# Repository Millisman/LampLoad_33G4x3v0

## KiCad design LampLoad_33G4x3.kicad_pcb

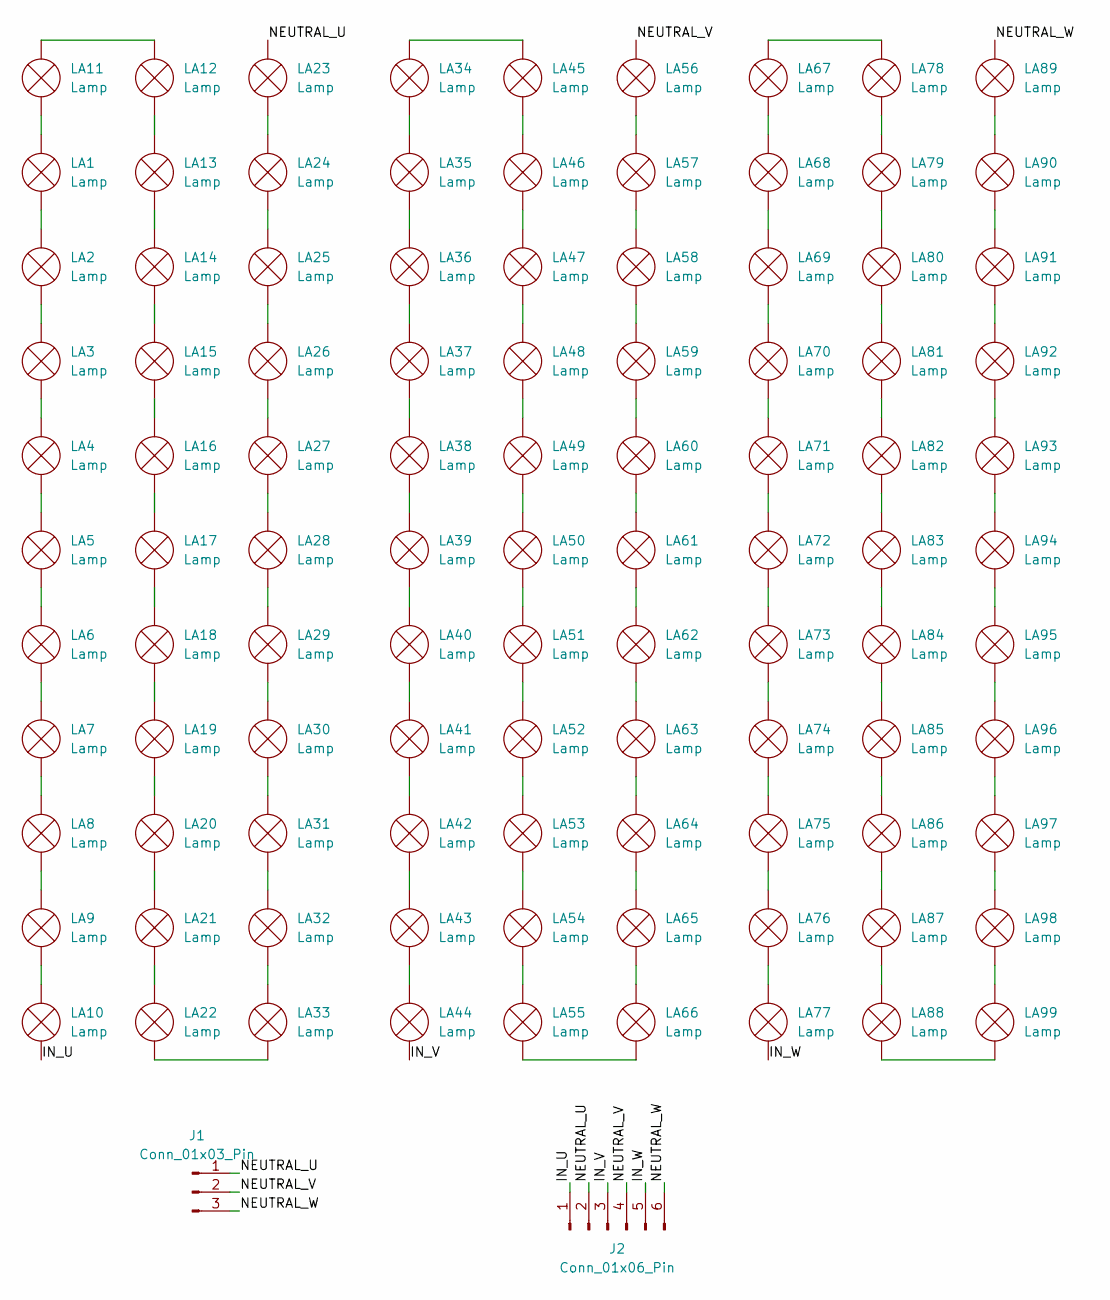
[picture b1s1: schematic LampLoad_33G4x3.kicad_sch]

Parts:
J1: Conn_01x03_Pin; PhoenixContact_MC_1,5_3-G-5.08_1x03_P5.08mm_Horizontal
J2: Conn_01x06_Pin; PhoenixContact_MC_1,5_6-G-5.08_1x06_P5.08mm_Horizontal
LA1, LA2, LA3, LA4, LA5, LA6, LA7, LA8, LA9, LA10, LA11, LA12, LA13, LA14, LA15, LA16, LA17, LA18, LA19, LA20, LA21, LA22, LA23, LA24, LA25, LA26, LA27, LA28, LA29, LA30, LA31, LA32, LA33, LA34, LA35, LA36, LA37, LA38, LA39, LA40, LA41, LA42, LA43, LA44, LA45, LA46, LA47, LA48, LA49, LA50, LA51, LA52, LA53, LA54, LA55, LA56, LA57, LA58, LA59, LA60, LA61, LA62, LA63, LA64, LA65, LA66, LA67, LA68, LA69, LA70, LA71, LA72, LA73, LA74, LA75, LA76, LA77, LA78, LA79, LA80, LA81, LA82, LA83, LA84, LA85, LA86, LA87, LA88, LA89, LA90, LA91, LA92, LA93, LA94, LA95, LA96, LA97, LA98, LA99: Lamp; PinHeader_1x02_P2.54mm_Vertical

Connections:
/IN_U: J2.1, LA10.1 (-)
/IN_V: J2.3, LA44.1 (-)
/IN_W: J2.5, LA77.1 (-)
/NEUTRAL_U: J1.1, J2.2, LA23.2 (+)
/NEUTRAL_V: J1.2, J2.4, LA56.2 (+)
/NEUTRAL_W: J1.3, J2.6, LA89.2 (+)
unnamed: LA1.2 (+), LA11.1 (-)
unnamed: LA1.1 (-), LA2.2 (+)
unnamed: LA2.1 (-), LA3.2 (+)
unnamed: LA3.1 (-), LA4.2 (+)
unnamed: LA4.1 (-), LA5.2 (+)
unnamed: LA5.1 (-), LA6.2 (+)
unnamed: LA6.1 (-), LA7.2 (+)
unnamed: LA7.1 (-), LA8.2 (+)
unnamed: LA8.1 (-), LA9.2 (+)
unnamed: LA9.1 (-), LA10.2 (+)
unnamed: LA11.2 (+), LA12.2 (+)
unnamed: LA12.1 (-), LA13.2 (+)
unnamed: LA13.1 (-), LA14.2 (+)
unnamed: LA14.1 (-), LA15.2 (+)
unnamed: LA15.1 (-), LA16.2 (+)
unnamed: LA16.1 (-), LA17.2 (+)
unnamed: LA17.1 (-), LA18.2 (+)
unnamed: LA18.1 (-), LA19.2 (+)
unnamed: LA19.1 (-), LA20.2 (+)
unnamed: LA20.1 (-), LA21.2 (+)
unnamed: LA21.1 (-), LA22.2 (+)
unnamed: LA22.1 (-), LA33.1 (-)
unnamed: LA23.1 (-), LA24.2 (+)
unnamed: LA24.1 (-), LA25.2 (+)
unnamed: LA25.1 (-), LA26.2 (+)
unnamed: LA26.1 (-), LA27.2 (+)
unnamed: LA27.1 (-), LA28.2 (+)
unnamed: LA28.1 (-), LA29.2 (+)
unnamed: LA29.1 (-), LA30.2 (+)
unnamed: LA30.1 (-), LA31.2 (+)
unnamed: LA31.1 (-), LA32.2 (+)
unnamed: LA32.1 (-), LA33.2 (+)
unnamed: LA34.2 (+), LA45.2 (+)
unnamed: LA34.1 (-), LA35.2 (+)
unnamed: LA35.1 (-), LA36.2 (+)
unnamed: LA36.1 (-), LA37.2 (+)
unnamed: LA37.1 (-), LA38.2 (+)
unnamed: LA38.1 (-), LA39.2 (+)
unnamed: LA39.1 (-), LA40.2 (+)
unnamed: LA40.1 (-), LA41.2 (+)
unnamed: LA41.1 (-), LA42.2 (+)
unnamed: LA42.1 (-), LA43.2 (+)
unnamed: LA43.1 (-), LA44.2 (+)
unnamed: LA45.1 (-), LA46.2 (+)
unnamed: LA46.1 (-), LA47.2 (+)
unnamed: LA47.1 (-), LA48.2 (+)
unnamed: LA48.1 (-), LA49.2 (+)
unnamed: LA49.1 (-), LA50.2 (+)
unnamed: LA50.1 (-), LA51.2 (+)
unnamed: LA51.1 (-), LA52.2 (+)
unnamed: LA52.1 (-), LA53.2 (+)
unnamed: LA53.1 (-), LA54.2 (+)
unnamed: LA54.1 (-), LA55.2 (+)
unnamed: LA55.1 (-), LA66.1 (-)
unnamed: LA56.1 (-), LA57.2 (+)
unnamed: LA57.1 (-), LA58.2 (+)
unnamed: LA58.1 (-), LA59.2 (+)
unnamed: LA59.1 (-), LA60.2 (+)
unnamed: LA60.1 (-), LA61.2 (+)
unnamed: LA61.1 (-), LA62.2 (+)
unnamed: LA62.1 (-), LA63.2 (+)
unnamed: LA63.1 (-), LA64.2 (+)
unnamed: LA64.1 (-), LA65.2 (+)
unnamed: LA65.1 (-), LA66.2 (+)
unnamed: LA67.2 (+), LA78.2 (+)
unnamed: LA67.1 (-), LA68.2 (+)
unnamed: LA68.1 (-), LA69.2 (+)
unnamed: LA69.1 (-), LA70.2 (+)
unnamed: LA70.1 (-), LA71.2 (+)
unnamed: LA71.1 (-), LA72.2 (+)
unnamed: LA72.1 (-), LA73.2 (+)
unnamed: LA73.1 (-), LA74.2 (+)
unnamed: LA74.1 (-), LA75.2 (+)
unnamed: LA75.1 (-), LA76.2 (+)
unnamed: LA76.1 (-), LA77.2 (+)
unnamed: LA78.1 (-), LA79.2 (+)
unnamed: LA79.1 (-), LA80.2 (+)
unnamed: LA80.1 (-), LA81.2 (+)
unnamed: LA81.1 (-), LA82.2 (+)
unnamed: LA82.1 (-), LA83.2 (+)
unnamed: LA83.1 (-), LA84.2 (+)
unnamed: LA84.1 (-), LA85.2 (+)
unnamed: LA85.1 (-), LA86.2 (+)
unnamed: LA86.1 (-), LA87.2 (+)
unnamed: LA87.1 (-), LA88.2 (+)
unnamed: LA88.1 (-), LA99.1 (-)
unnamed: LA89.1 (-), LA90.2 (+)
unnamed: LA90.1 (-), LA91.2 (+)
unnamed: LA91.1 (-), LA92.2 (+)
unnamed: LA92.1 (-), LA93.2 (+)
unnamed: LA93.1 (-), LA94.2 (+)
unnamed: LA94.1 (-), LA95.2 (+)
unnamed: LA95.1 (-), LA96.2 (+)
unnamed: LA96.1 (-), LA97.2 (+)
unnamed: LA97.1 (-), LA98.2 (+)
unnamed: LA98.1 (-), LA99.2 (+)

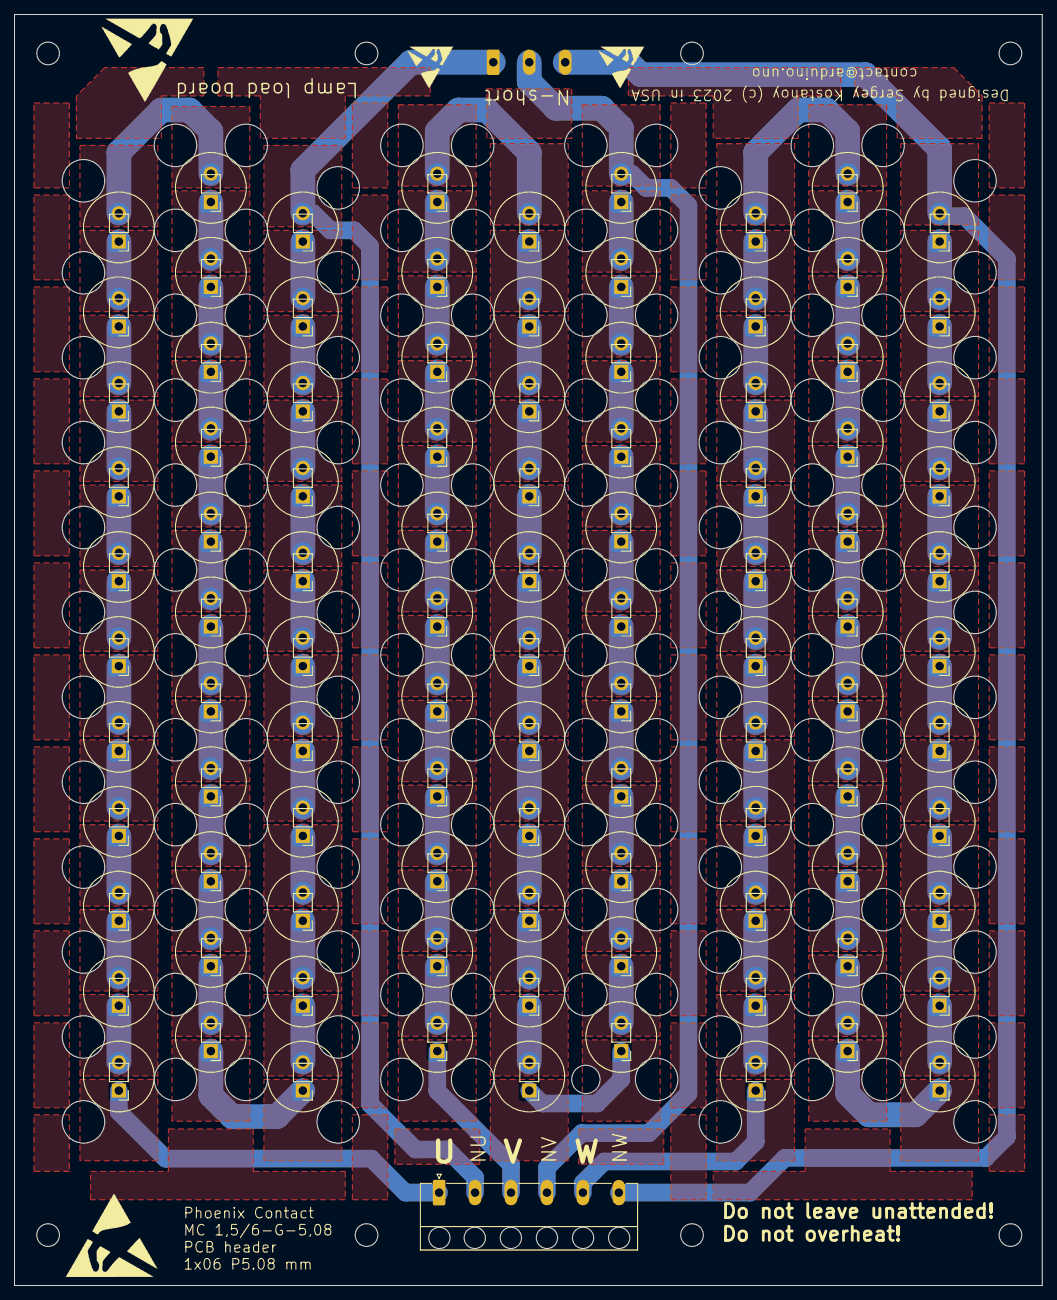
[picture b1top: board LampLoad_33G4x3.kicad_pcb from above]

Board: 2 copper layers, 145.2 x 179.6 mm, 101 parts (1 on the bottom side), 102 nets.

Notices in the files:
LampLoad_33G4x3.kicad_pcb:
Designed by Sergey Kostanoy (c) 2023 in USA
